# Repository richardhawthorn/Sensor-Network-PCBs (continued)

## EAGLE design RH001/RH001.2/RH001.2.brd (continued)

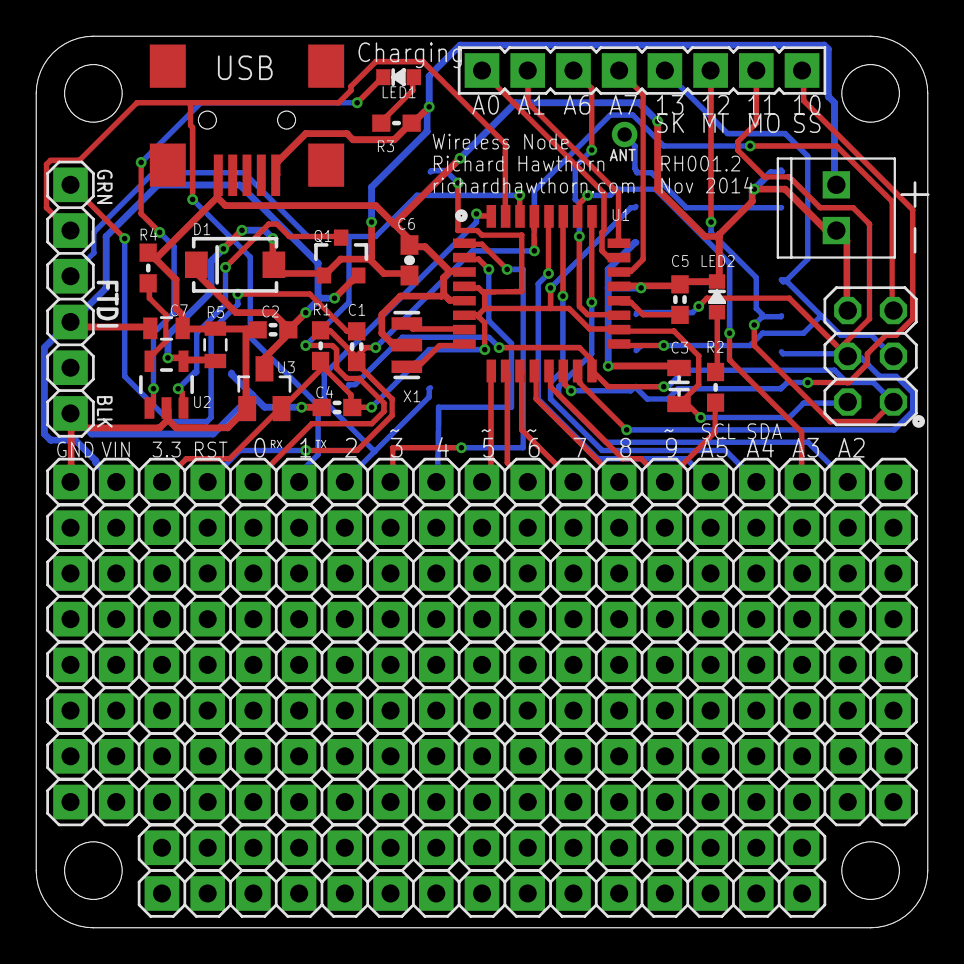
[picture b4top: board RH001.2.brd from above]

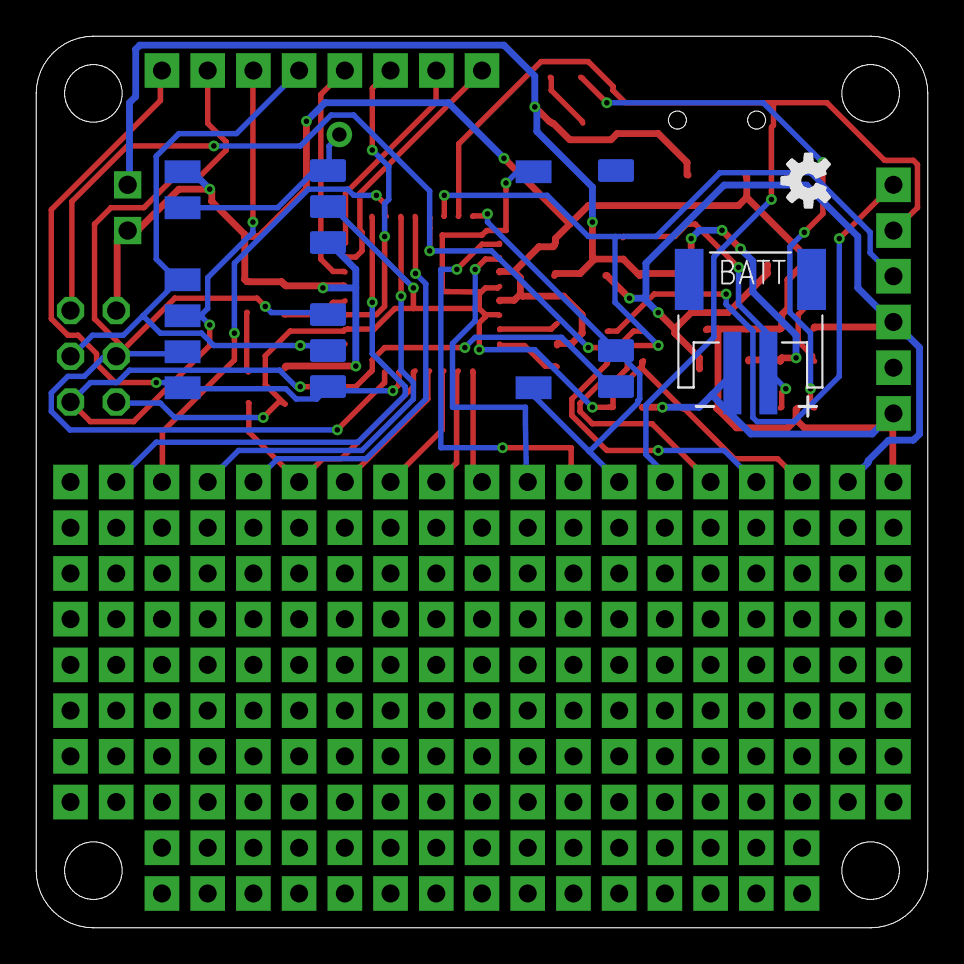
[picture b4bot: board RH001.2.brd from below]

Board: 2 copper layers, 49.5 x 49.5 mm, 40 parts (4 on the bottom side), 37 nets.

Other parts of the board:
U$3: OSHW-LOGO-S

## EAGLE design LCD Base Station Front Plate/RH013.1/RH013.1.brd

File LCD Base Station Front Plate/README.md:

### Features

Front plate for LCD base station

- 12x capacitive buttons
- Space for 128x64 LCD
- Connection to base station

### Buttons

##### LCD

- Top Left
- Bottom Left
- Top Right
- Bottom Right

##### Directional

- Up
- Down
- Left
- Right

##### General

- Home
- Menu
- Enter
- Cancel

### Layout
```
 __________________________________
|      ______________________      |
|  _  |                      |  _  |
| |_| |                      | |_| |
|  _  |                      |  _  | 
| |_| |                      | |_| |
|     |______________________|     |
|           _         _   _        |    
|         _|_|_      |_| |_|       |
|        |_|_|_|      _   _        |
|          |_|       |_| |_|       |
|__________________________________|

```

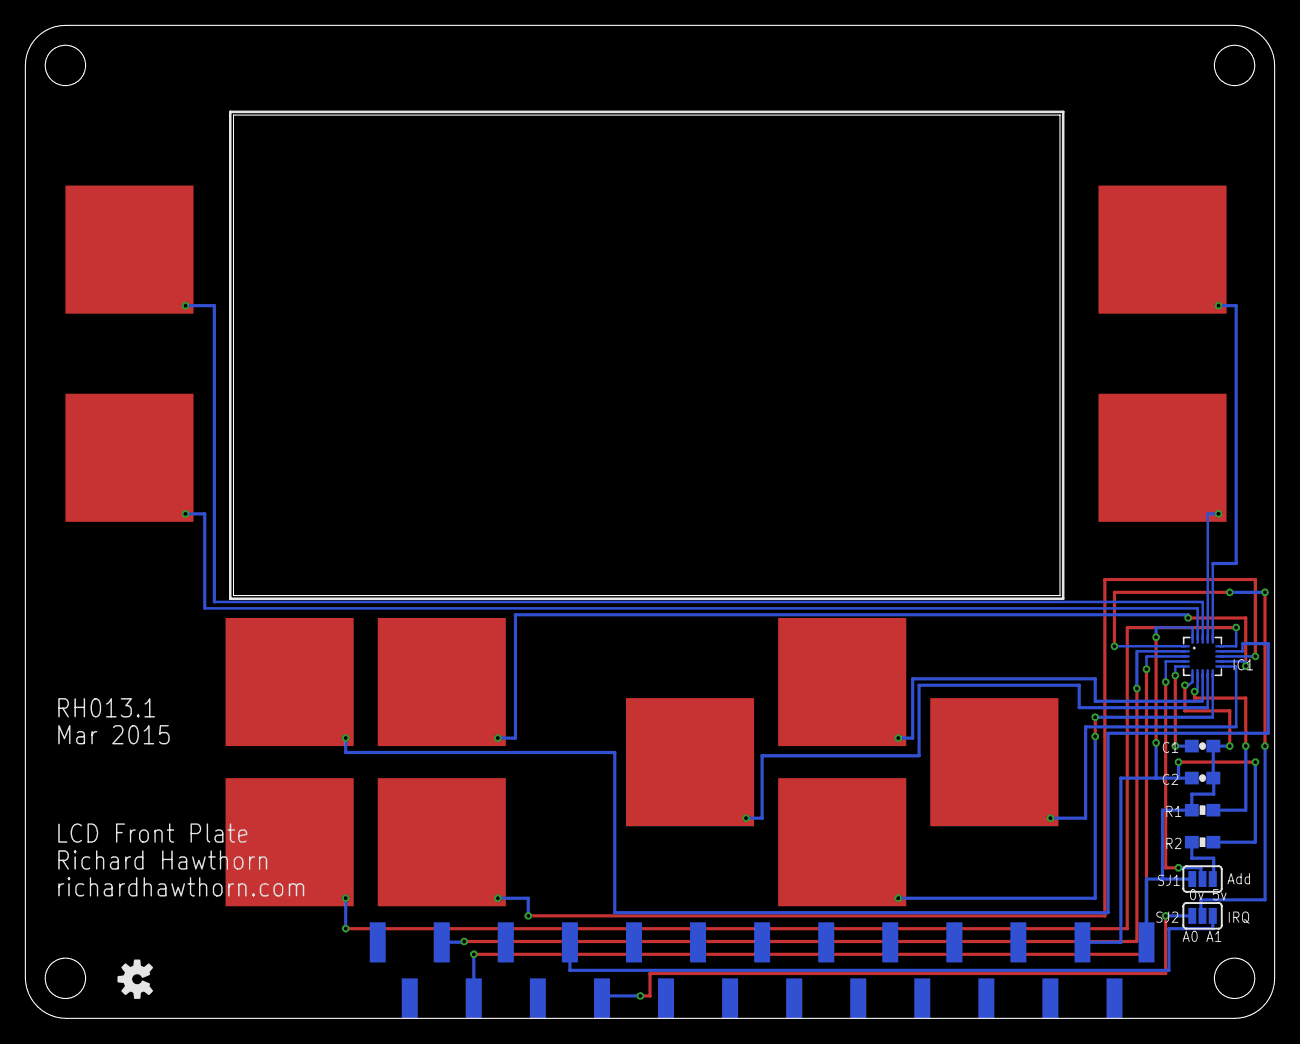
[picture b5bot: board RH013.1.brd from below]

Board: 2 copper layers, 99.1 x 78.7 mm, 10 parts (10 on the bottom side), 11 nets.

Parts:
C1, C2: 0.1uF; 0603-CAP
IC1: MPR121; QFN-20-0.4MM-V2
R1: 75k; 0603-RES
R2: 10K; 0603-RES
SJ1, SJ2: SJ_3_PASTE1&2
U$3: OSHW-LOGO-S
X1: C-GRID-14-74099; 74099-14
X2: C-GRID-11-74099; 74099-11

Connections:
3.3V: C2.1, IC1.20, R2.2, X1.12
A0: SJ2.1, X2.4
A1: SJ2.3, X2.5
A4_SDA: IC1.3, X2.8
A5_SCL: IC1.2, X2.9
GND: C1.2, C2.2, IC1.6, R1.1, SJ1.1, X1.14
unnamed: IC1.4, SJ1.2
unnamed: R2.1, SJ1.3
REXT: IC1.7, R1.2
VREG: C1.1, IC1.5
~IRQ: IC1.1, SJ2.2

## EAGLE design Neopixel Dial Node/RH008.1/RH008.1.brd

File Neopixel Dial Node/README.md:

# Neopixel Dial Node

A ring of 16 neopixels around a rotary encoder

```
###################################
#                                 #
#   Board not fully routed yet    #
#                                 #
###################################
```

### Other Features

- ATMEGA328P with Arduino boot-loader
- RMF12B/RFM69W radio
- 3.3V operation
- Mini USB power connector
- FTDI programming port
- LED output
- FTDI programming port

### Potential Uses

##### With rotary encoder

Control and visualise

- Volume 
- Temperature 
- Light

##### Without rotary encoder

Visualise

- Time
- Temperature
- Humidity
- Bandwidth
- Server load

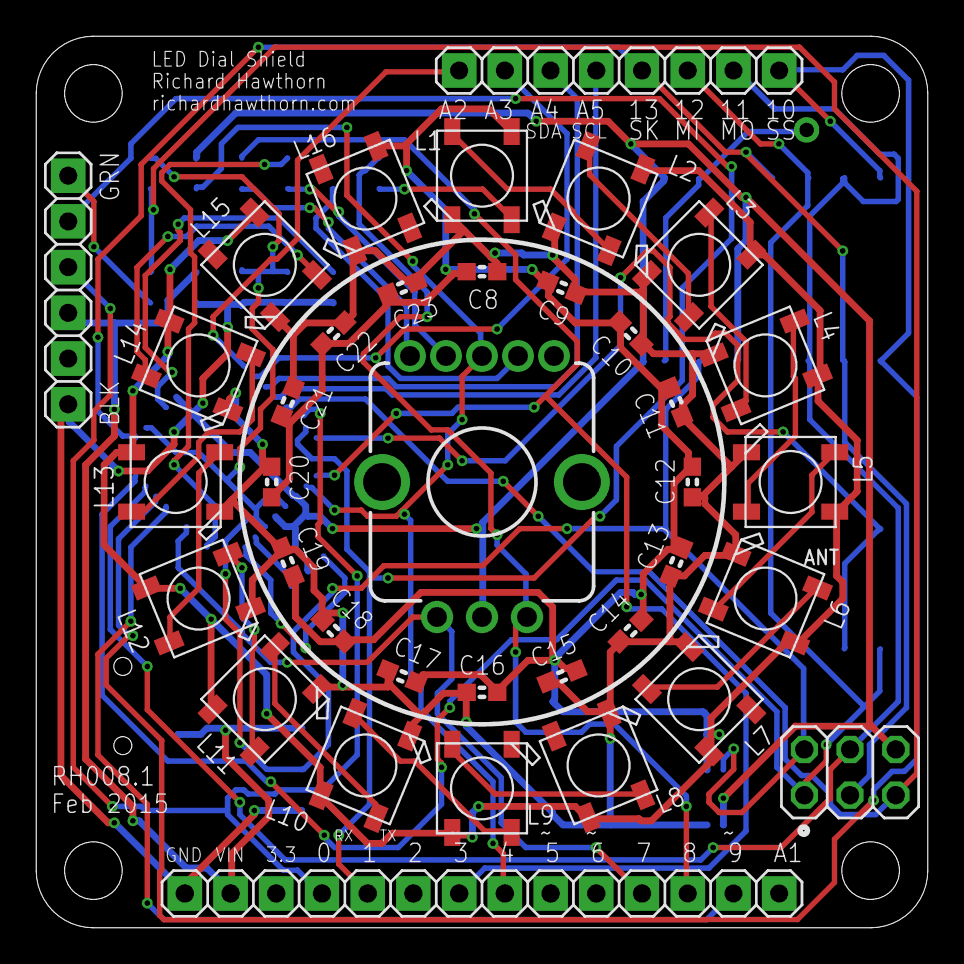
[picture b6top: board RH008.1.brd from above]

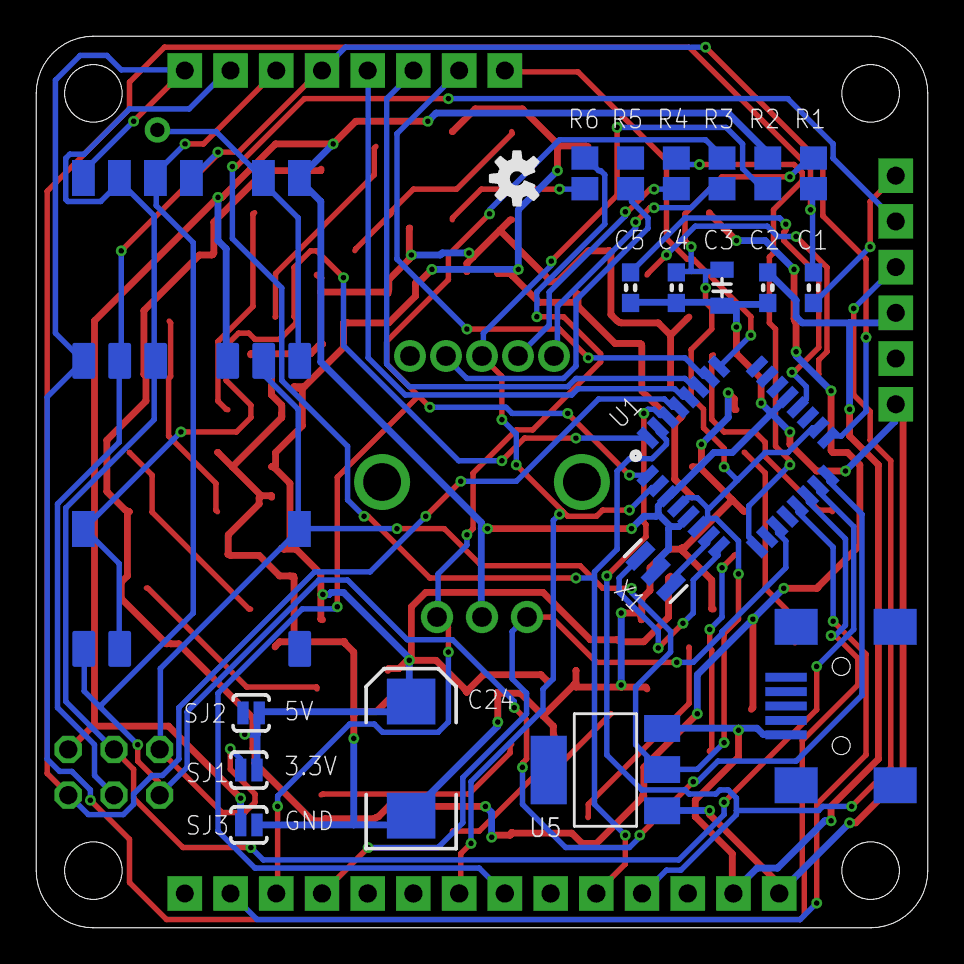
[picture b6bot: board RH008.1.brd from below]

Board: 2 copper layers, 49.5 x 49.5 mm, 60 parts (22 on the bottom side), 49 nets.

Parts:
C1, C4, C5, C8, C9, C10, C11, C12, C13, C14, C15, C16, C17, C18, C19, C20, C21, C22, C23: 0.1; 0603-CAP
C2: 1u; 0603-CAP
C3: 10u; 0805-CAP
C24: 100uF; EIA7343
CN1: USB; USB-MINIB
CN4: FTDI; 1X06
ICSP1: ICSP; 2X03
JP3: 1X14
JP5: 1X08
L1, L2, L3, L4, L5, L6, L7, L8, L9, L10, L11, L12, L13, L14, L15, L16: WS2812B
R1, R2: 10k; R0805
R3: 300; R0805
R4, R5: 180; R0805
R6: 100r; R0805
RF1: RFM12B; RFM12B-MINPADS
RF2: RFM69; RFM69W-MINPADS
SJ1, SJ2, SJ3: SOLDERJUMPERNO; SJ_2S-NO
U1: ATMega-328; TQFP32-08
U4: ENCODER_RGB; ENCODER_LED_RGB
U5: REG1117; SOT223
U$1: RFM12B_ANTENNA; RFM12B-ANTENNA
U$3: OSHW-LOGO-S
X1: 16 MHz; RESONATOR-SMD

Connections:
A1: JP3.1, U1.24
A2: JP5.1, U1.25
A3: JP5.2, U1.26
A4_SDA: JP5.3, U1.27
A5_SCL: JP5.4, U1.28
AREF: C5.1, U1.20
D0_RX: CN4.4, JP3.11, U1.30
D1_TX: CN4.5, JP3.10, U1.31
D2: JP3.9, RF1.IRQ, RF2.DIO0, U1.32
D3: JP3.8, R3.2, U1.1
D4: JP3.7, R2.2, U1.2, U4.SW
D5: JP3.6, R4.2, U1.9
D6: JP3.5, R5.2, U1.10
D7: JP3.4, U1.11, U4.A
D8: JP3.3, R6.1, U1.12, U4.B
D9: JP3.2, U1.13
D10_SS: JP5.8, RF1.SEL, RF2.NSS, U1.14
D11_MOSI: ICSP1.4, JP5.7, RF1.SDI, RF2.MOSI, U1.15
D12_MISO: ICSP1.1, JP5.6, RF1.SDO, RF2.MISO, U1.16
D13_SCK: ICSP1.3, JP5.5, RF1.SCK, RF2.SCK, U1.17
GND: C2.2, C3.2, C4.2, C5.2, CN1.GND, CN4.1, ICSP1.6, JP3.14, R2.1, RF1.GND, RF2.GND, SJ3.1, U1.3, U1.5, U1.21, U4.C, U5.1, X1.2
LED-B: R5.1, U4.BL
LED-G: R4.1, U4.G
LED-MID-1: L5.2-DOUT, L6.4-DIN
LED-MID-2: L7.2-DOUT, L8.4-DIN
LED-MID-3: L9.2-DOUT, L10.4-DIN
LED-OUT-1: L1.2-DOUT, L2.4-DIN
LED-OUT-2: L3.2-DOUT, L4.4-DIN
LED-OUT-3: L4.2-DOUT, L5.4-DIN
LED-OUT-4: L12.2-DOUT, L13.4-DIN
LED-OUT-5: L13.2-DOUT, L14.4-DIN
LED-OUT-6: L15.2-DOUT, L16.4-DIN
LED-R: R3.1, U4.R
LED_DATA: L1.4-DIN, R6.2
LED_NEG: C8.2, C9.2, C10.2, C11.2, C12.2, C13.2, C14.2, C15.2, C16.2, C17.2, C18.2, C19.2, C20.2, C21.2, C22.2, C23.2, C24.C, L1.3-GND, L2.3-GND, L3.3-GND, L4.3-GND, L5.3-GND, L6.3-GND, L7.3-GND, L8.3-GND, L9.3-GND, L10.3-GND, L11.3-GND, L12.3-GND, L13.3-GND, L14.3-GND, L15.3-GND, L16.3-GND, SJ3.2
LED_POS: C8.1, C9.1, C10.1, C11.1, C12.1, C13.1, C14.1, C15.1, C16.1, C17.1, C18.1, C19.1, C20.1, C21.1, C22.1, C23.1, C24.A, L1.1-VDD, L2.1-VDD, L3.1-VDD, L4.1-VDD, L5.1-VDD, L6.1-VDD, L7.1-VDD, L8.1-VDD, L9.1-VDD, L10.1-VDD, L11.1-VDD, L12.1-VDD, L13.1-VDD, L14.1-VDD, L15.1-VDD, L16.1-VDD, SJ1.2, SJ2.2
unnamed: L2.2-DOUT, L3.4-DIN
unnamed: L6.2-DOUT, L7.4-DIN
unnamed: L8.2-DOUT, L9.4-DIN
unnamed: L10.2-DOUT, L11.4-DIN
unnamed: L11.2-DOUT, L12.4-DIN
unnamed: U1.7, X1.1
unnamed: RF1.ANT, RF2.ANA, U$1.P$1
unnamed: L14.2-DOUT, L15.4-DIN
unnamed: C1.2, CN4.6
unnamed: U1.8, X1.3
RST: C1.1, ICSP1.5, R1.2, U1.29
VBUS: C2.1, CN1.VBUS, CN4.3, JP3.13, SJ2.1, U5.3
VCC: C3.1, C4.1, ICSP1.2, R1.1, RF1.VDD, RF2.VDD, SJ1.1, U1.4, U1.6, U1.18, U4.VCC, U5.2

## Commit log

2015-02-11 ignore old versions
2015-02-11 Adding board 1.1 - prototype node
2015-02-11 2nd version of photo node
2015-02-11 Electric imp base station
2015-02-11 Sensor Node
2015-02-11 Neopixel node
2015-02-11 7 segment node
2015-02-11 14 segment alpha node
2015-02-11 Clock 1.1
2015-02-11 mono matrix shield
2015-02-11 bi colour matrix shield
2015-02-12 Minor tweaks to board 006
2015-02-12 Finished the routing and fixed led power
2015-02-12 Minor fixes
2015-03-27 Prepare board 6 for production, version 1 finished
2015-03-27 update gitignore
2015-03-27 Board 7.1 finished
2015-03-27 Board 9.1 finished
2015-03-27 Ready for production
2015-03-27 Sure 3208 driver board added
2015-03-27 LCD driver board
2015-03-27 LCD front plate
2015-03-27 First rough version of an rgb led dial
2015-06-07 moving clock to it's own repo
2015-06-07 Prototype Node
2015-06-07 Base Station
2015-06-07 14 Segment Node
2015-06-07 Neopixel Dial Node
2015-06-07 8x8 Matrix Shield
2015-06-07 8x8 2-Colour Matrix Shield
2015-06-07 3208 Matrix Node
2015-06-07 LCD Base Station
2015-06-07 LCD Base Station Front Plate
2015-06-16 Add readme for front plate
2015-06-16 update main readme
2015-06-16 Add board images
2015-06-16 add images to readme
2015-06-16 Front plate update
2015-06-16 Update readme files
2015-06-16 Base station update
2015-06-16 Readme updates
2015-07-02 moved pcb files
2015-07-02 updated sensor node readme
2015-07-02 copy fix
2015-07-03 added photos
2015-07-03 add additional image
2015-07-03 move pcb files
2015-07-03 update details for base station front plate
2015-07-03 updated LCD base station files
2015-07-03 add extra image
2015-07-03 add images and move pcb files
2015-07-03 add images and move files
2015-07-03 add photos
2015-07-03 adding photos
2015-07-03 moving images to correct location
2015-08-05 added prototype photos
2015-08-05 move prototype node files
2016-01-03 add images for 7 segment node
